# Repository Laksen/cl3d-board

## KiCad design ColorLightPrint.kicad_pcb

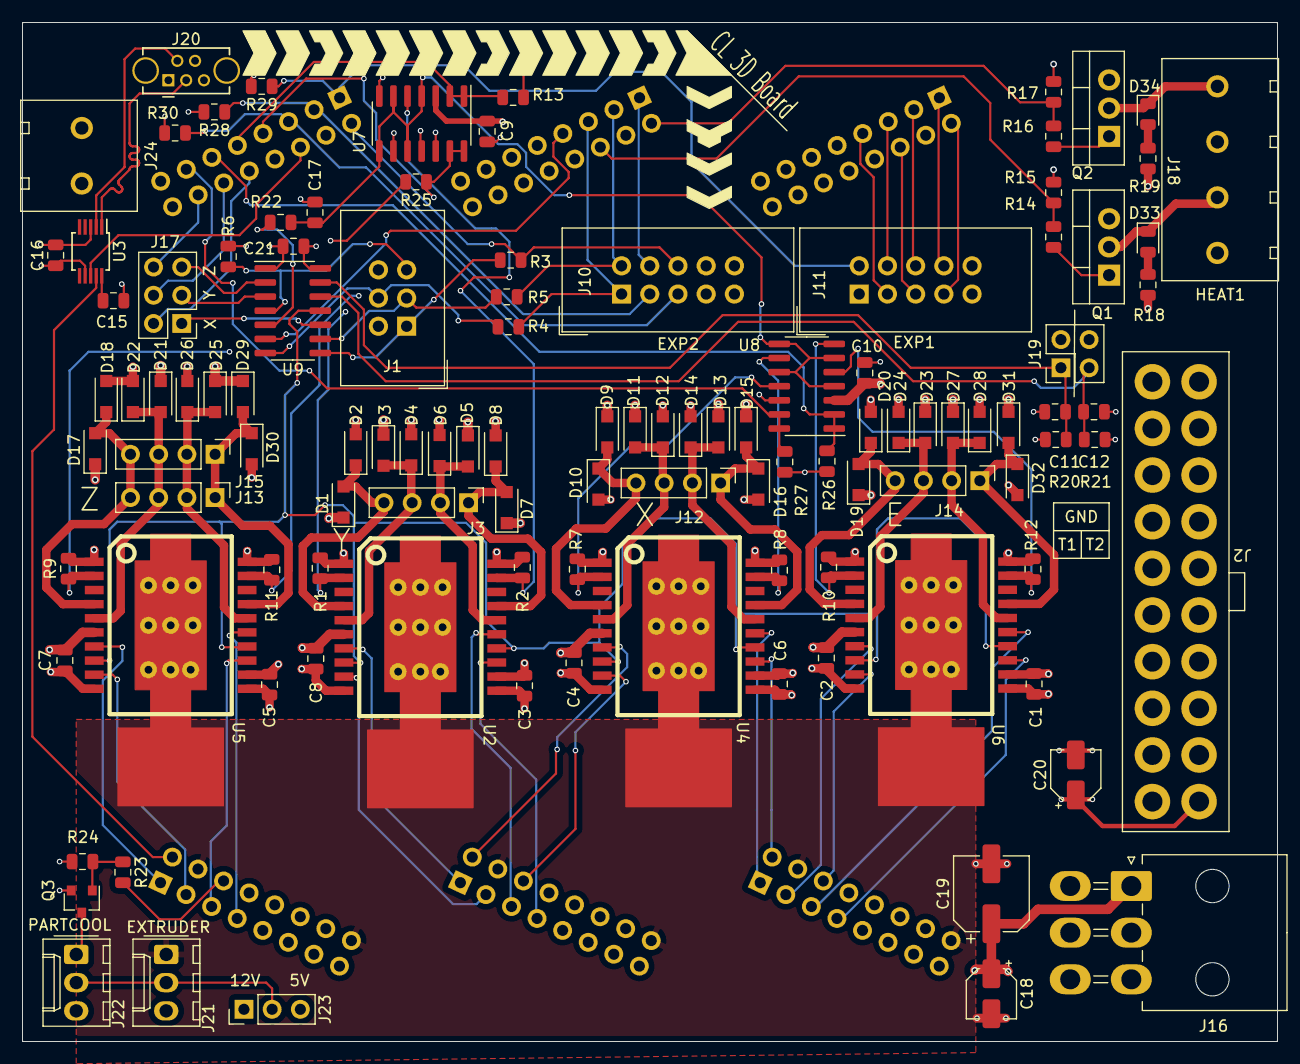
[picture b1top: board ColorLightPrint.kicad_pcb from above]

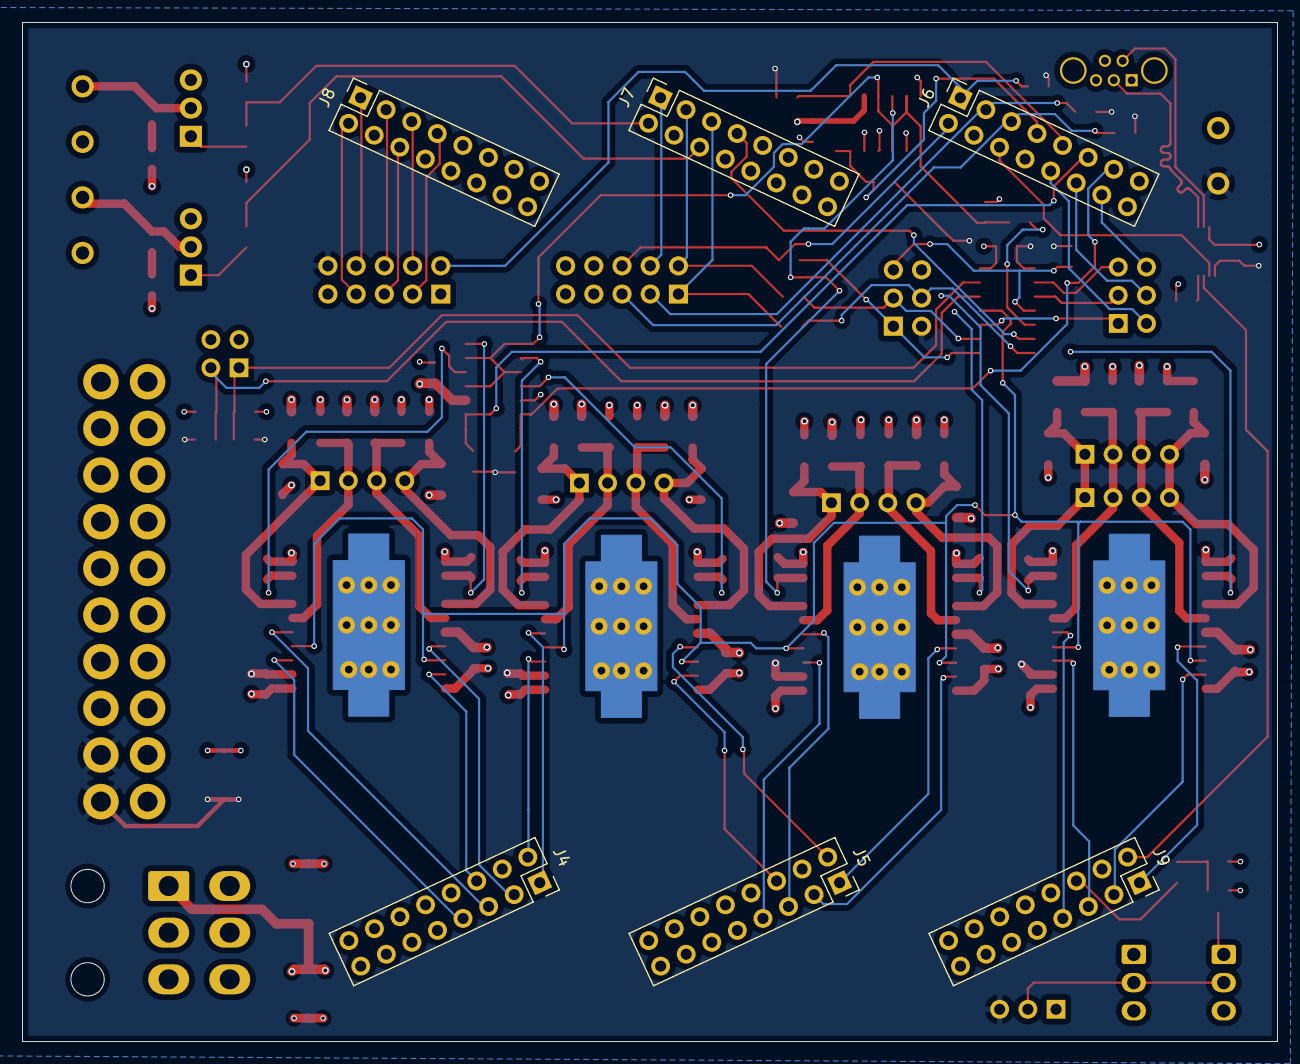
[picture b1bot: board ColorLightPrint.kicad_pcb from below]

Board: 4 copper layers, 113.0 x 91.8 mm, 118 parts (6 on the bottom side), 93 nets.

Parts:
C1, C2, C3, C4, C5, C6, C7, C8, C9, C10, C15, C16, C17, C21: 100nF; C_0805_2012Metric
C11, C12: 10uF; C_0805_2012Metric
C18, C20: 10uF; CP_Elec_4x5.3
C19: 100uF; CP_Elec_6.3x7.7
D1, D2, D3, D4, D5, D6, D7, D8, D9, D10, D11, D12, D13, D14, D15, D16, D17, D18, D19, D20, D21, D22, D23, D24, D25, D26, D27, D28, D29, D30, D31, D32: D; D_SOD-123F
D33, D34: LED_Small; LED_0805_2012Metric
J1: AVR-ISP-6; IDC-Header_2x03_P2.54mm_Vertical
J2: Conn_02x10_Counter_Clockwise; 87427-2042
J3, J12, J13, J14, J15: Conn_01x04_Male; PinHeader_1x04_P2.54mm_Vertical
J4, J5, J6, J7, J8, J9: Conn_02x08_Odd_Even; PinSocket_Center
J10: EXP2; IDC-Header_2x05_P2.54mm_Vertical
J11: EXP1; IDC-Header_2x05_P2.54mm_Vertical
J16: Conn_02x03_Counter_Clockwise; Molex_Mini-Fit_Jr_5569-06A2_2x03_P4.20mm_Horizontal
J17: Conn_02x03_Odd_Even; PinHeader_2x03_P2.54mm_Vertical
J18: Heaters; WJ128V-5.0-4P
J19: Therm; PinHeader_2x02_P2.54mm_Vertical
J20: USB_B_Mini; USB_Mini-B_Tensility_54-00023_Vertical_CircularHoles
J21: ExtruderFan; Molex_KK-254_AE-6410-03A_1x03_P2.54mm_Vertical
J22: PartCooling; Molex_KK-254_AE-6410-03A_1x03_P2.54mm_Vertical
J23: Conn_01x03_Male; PinHeader_1x03_P2.54mm_Vertical
J24: +5V; WJ126V-5.0-2P
Q1, Q2: STP55; TO-220-3_Vertical
Q3: AO3400A; SOT-23
R1, R2, R7, R8, R9, R10, R11, R12: 0.5; R_0805_2012Metric
R3, R4, R5: 120; R_0805_2012Metric
R6, R13, R20, R21, R22, R23, R25, R26, R27, R28, R29, R30: 4.7k; R_0805_2012Metric
R14, R16: 10; R_0805_2012Metric
R15, R17, R24: 100k; R_0805_2012Metric
R18, R19: 500; R_0805_2012Metric
U2, U4, U5, U6: L298P; PowerSO20
U3: CH340E; MSOP-10_3x3mm_P0.5mm
U7, U8: LM339; SOIC-14_3.9x8.7mm_P1.27mm
U9: ATtiny44A-SSU; SOIC-14_3.9x8.7mm_P1.27mm

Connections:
+12V: C2.1, C4.1, C7.1, C8.1, C9.1, C10.1, C18.1, C19.1, D1.1, D3.1, D5.1, D7.1, D9.1, D11.1, D13.1, D15.1, D17.1, D19.1, D21.1, D23.1, D25.1, D27.1, D29.1, D31.1, J2.10, J16.1, J16.2, J16.3, J18.2, J18.4, J23.1, R18.1, R19.1, U2.6, U4.6, U5.6, U6.6, U7.3, U8.3
/ENC_BTN: J6.1, J11.2, R29.1
/ENC_D0: J6.5, J10.5, R30.1
/ENC_D1: J6.3, J10.3, R28.1
/ENDPULL_X: J17.1, U9.10
/ENDPULL_Y: J17.3, U9.3
/ENDPULL_Z: J17.5, U9.2
/END_X: J6.10, J17.2
/END_Y: J6.12, J17.4
/END_Z: J6.14, J17.6
/FAN: J9.6, R23.2
/HEAT1: J7.6, R14.2, R15.2
/HEAT1_DRV: D33.1, J18.3, Q1.2
/HEAT2: J7.2, R16.2, R17.2
/HEAT2_DRV: D34.1, J18.1, Q2.2
/ISP_MISO: J1.1, R3.1, U9.8
/ISP_MOSI: J1.4, R4.1, U9.7
/ISP_SCK: J1.3, R5.1, U9.9
/ISP_SS: J7.7, U9.6
/LCD4: J8.6, J11.5
/LCD5: J8.3, J11.6
/LCD6: J8.2, J11.7
/LCD7: J8.1, J11.8
/LCDE: J8.7, J11.3
/LCDRS: J8.5, J11.4
/RS232_RX: J9.2, U3.9
/RS232_TX: J6.6, U3.8
/S0_1: J5.1, U2.7
/S0_2: J5.3, U2.9
/S0_3: J5.7, U2.13
/S0_4: J5.5, U2.15
/S0_A: R1.1, U2.2, U7.7
/S0_B: R2.1, U2.19, U7.5
/S1_1: J9.1, U5.7
/S1_2: J9.3, U5.9
/S1_3: J9.5, U5.13
/S1_4: J9.7, U5.15
/S1_A: R9.1, U5.2, U7.9
/S1_B: R11.1, U5.19, U7.11
/S2_1: J5.2, U4.7
/S2_2: J5.6, U4.9
/S2_3: J4.2, U4.13
/S2_4: J4.1, U4.15
/S2_A: R7.1, U4.2, U8.11
/S2_B: R8.1, U4.19, U8.9
/S3_1: J4.3, U6.7
/S3_2: J4.6, U6.9
/S3_3: J4.7, U6.13
/S3_4: J4.5, U6.15
/S3_A: R10.1, U6.2, U8.7
/S3_B: R12.1, U6.19, U8.5
/SD_CS: J7.1, J10.4
/SPI_MISO: J6.2, J10.6, R3.2
/SPI_MOSI: J7.5, J10.1, R4.2
/SPI_SCK: J7.3, J10.2, R5.2
/STEP0_1: D1.2, D2.1, J3.4, U2.4
/STEP0_2: D3.2, D4.1, J3.3, U2.5
/STEP0_3: D5.2, D6.1, J3.2, U2.16
/STEP0_4: D7.2, D8.1, J3.1, U2.17
/STEP1_1: D17.2, D18.1, J13.4, J15.4, U5.4
/STEP1_2: D21.2, D22.1, J13.3, J15.3, U5.5
/STEP1_3: D25.2, D26.1, J13.2, J15.2, U5.16
/STEP1_4: D29.2, D30.1, J13.1, J15.1, U5.17
/STEP2_1: D9.2, D10.1, J12.4, U4.4
/STEP2_2: D11.2, D12.1, J12.3, U4.5
/STEP2_3: D13.2, D14.1, J12.2, U4.16
/STEP2_4: D15.2, D16.1, J12.1, U4.17
/STEP3_1: D19.2, D20.1, J14.4, U6.4
/STEP3_2: D23.2, D24.1, J14.3, U6.5
/STEP3_3: D27.2, D28.1, J14.2, U6.16
/STEP3_4: D31.2, D32.1, J14.1, U6.17
/STEP_ENABLE: U2.8, U2.14, U4.8, U4.14, U5.8, U5.14, U6.8, U6.14, U9.11
/S_CURRENT_E: J6.11, R26.1, U8.1, U8.2
/S_CURRENT_LIMIT: C17.1, R22.2, U7.4, U7.6, U7.8, U7.10, U8.4, U8.6, U8.8, U8.10
/S_CURRENT_X: J6.13, R27.1, U8.13, U8.14
/S_CURRENT_Y: J6.9, R13.1, U7.1, U7.2
/S_CURRENT_Z: J6.7, R25.1, U7.13, U7.14
/S_PWM: R22.1, U9.5
/THERM1: C11.1, J19.1, R20.2, U9.13
/THERM2: C12.1, J19.3, R21.1, U9.12
/USB_N: J20.2, U3.2
/USB_P: J20.3, U3.1
/~ISP_RESET: J1.5, R6.2, U9.4
GND: C1.2, C2.2, C3.2, C4.2, C5.2, C6.2, C7.2, C8.2, C9.2, C10.2, C11.2, C12.2, C15.2, C16.2, C17.2, C18.2, C19.2, C20.2, C21.2, D2.2, D4.2, D6.2, D8.2, D10.2, D12.2, D14.2, D16.2, D18.2, D20.2, D22.2, D24.2, D26.2, D28.2, D30.2, D32.2, J1.6, J2.3, J2.5, J2.7, J2.14, J2.15, J2.16, J2.17, J2.18, J4.4, J4.16, J5.4, J5.16, J6.4, J6.15, J6.16, J7.4, J7.16, J8.4, J8.16, J9.4, J9.16, J11.9, J16.4, J16.5, J16.6, J19.2, J19.4, J20.5, J20.6, J21.1, J24.2, Q1.3, Q2.3, Q3.2, R1.2, R2.2, R7.2, R8.2, R9.2, R10.2, R11.2, R12.2, R15.1, R17.1, R24.2, U2.1, U2.10, U2.11, U2.20, U3.3, U4.1, U4.10, U4.11, U4.20, U5.1, U5.10, U5.11, U5.20, U6.1, U6.10, U6.11, U6.20, U7.12, U8.12, U9.14
unnamed: C15.1, U3.10
unnamed: D33.2, R18.2
unnamed: D34.2, R19.2
unnamed: J22.1, Q3.3
unnamed: Q1.1, R14.1
unnamed: Q2.1, R16.1
unnamed: Q3.1, R23.1, R24.1
VCC: C1.1, C3.1, C5.1, C6.1, C16.1, C20.1, C21.1, J1.2, J2.11, J2.12, J11.10, J23.3, J24.1, R6.1, R13.2, R20.1, R21.2, R25.2, R26.2, R27.2, R28.2, R29.2, R30.2, U2.12, U3.7, U4.12, U5.12, U6.12, U9.1
VDD: J21.2, J22.2, J23.2

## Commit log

2020-04-01 Initial board revision.
2020-04-01 doc: Add rev0 schematic.
